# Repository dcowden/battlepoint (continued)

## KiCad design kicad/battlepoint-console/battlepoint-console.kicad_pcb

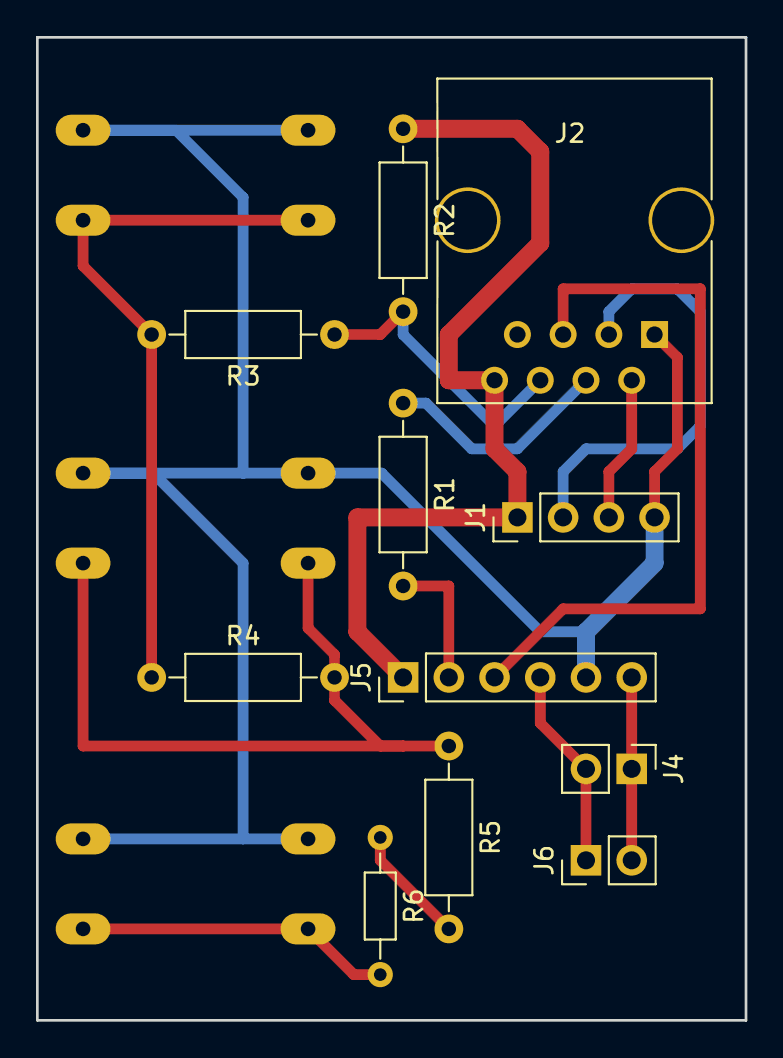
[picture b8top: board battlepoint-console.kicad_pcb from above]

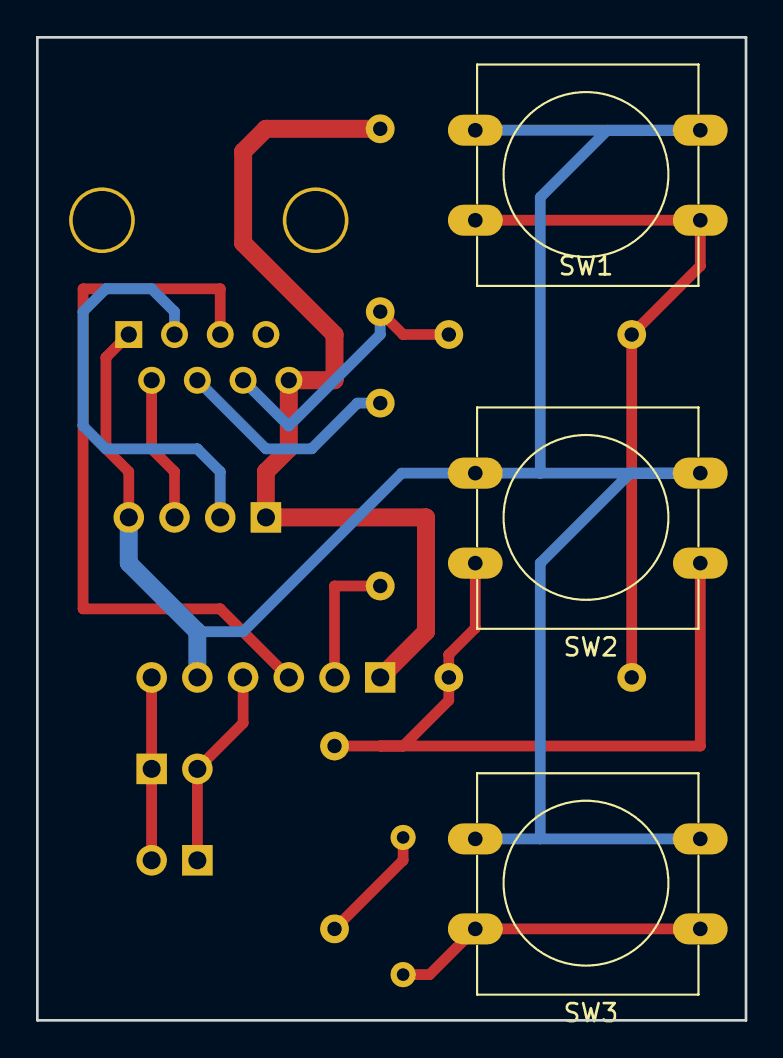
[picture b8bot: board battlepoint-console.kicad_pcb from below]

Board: 2 copper layers, 39.4 x 54.6 mm, 14 parts (3 on the bottom side), 14 nets.

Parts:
J1: OLED; Pin_Header_Straight_1x04_Pitch2.54mm
J2: TOMAIN; RJ45_8
J4: SPK; Pin_Header_Straight_1x02_Pitch2.54mm
J5: DFP; Pin_Header_Straight_1x06_Pitch2.54mm
J6: EXT_AUD; Pin_Header_Straight_1x02_Pitch2.54mm
R1, R5: 1K; R_Axial_DIN0207_L6.3mm_D2.5mm_P10.16mm_Horizontal
R2: 2K; R_Axial_DIN0207_L6.3mm_D2.5mm_P10.16mm_Horizontal
R3: 330; R_Axial_DIN0207_L6.3mm_D2.5mm_P10.16mm_Horizontal
R4: 620; R_Axial_DIN0207_L6.3mm_D2.5mm_P10.16mm_Horizontal
R6: 3.3K; R_Axial_DIN0204_L3.6mm_D1.6mm_P7.62mm_Horizontal
SW1: SW_UP; SW_PUSH-12mm
SW2: SW_DOWN; SW_PUSH-12mm
SW3: SW_SELECT; SW_PUSH-12mm

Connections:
+5V: J1.1, J2.8, J5.1, R2.1
A0: J2.6, R2.2, R3.1
GND: J1.4, J2.1, J5.5, SW1.2, SW2.2, SW3.2
unnamed: J1.2, J2.3
unnamed: J1.3, J2.2
unnamed: J2.4, R1.1
unnamed: J2.5, J5.3
unnamed: J5.2, R1.2
unnamed: R3.2, R4.1, SW1.1
unnamed: R4.2, R5.1, SW2.1
unnamed: R5.2, R6.1
unnamed: R6.2, SW3.1
SPK+: J4.2, J5.4, J6.1
SPK-: J4.1, J5.6, J6.2

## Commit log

2017-11-23 initial version
2017-11-23 vscode
2017-11-23 removed duplicate
2017-11-23 test commit
2017-11-23 another test commit
2017-11-23 removed duplciate
2017-12-03 trying to get nodemcu to work
2017-12-06 added kicad stuff
2017-12-07 working mostly
2017-12-07 progress
2017-12-07 about to start routing
2017-12-08 finished for now i think
2017-12-09 used rj45s for connections
2017-12-09 moved stuff
2017-12-09 more compact layout
2017-12-09 made button board fit
2017-12-10 got button board working
2017-12-15 base version without regulator
2017-12-15 add regulator circuit
2017-12-15 made the pads bigger
2017-12-17 version 1.0
2017-12-17 reversed the top layer
2017-12-17 fix missing traces on front
2017-12-23 version 1.2 finally ready!
2017-12-23 added todo
2017-12-23 more todo
2017-12-23 starting to clean up the code
2017-12-23 new boards
2017-12-23 suggestions for next version
2017-12-23 new script
2017-12-23 small mods to sound script
2017-12-30 changed to usb connectors
2017-12-31 routed
2018-01-01 finished routing
2018-06-03 added ledmeter
2018-06-03 mostly compiles now
2018-06-18 working on unit testing
2018-06-18 tests pass now
2018-06-18 tests working, nicer now
2018-06-18 added test for initial state
2018-06-20 working on refactoring
2018-06-21 a bit more progress
2018-06-22 more progress
2018-06-23 most control point tests working now
2018-06-23 timer and game audio passing tests now
2018-06-24 started on game
2018-06-24 most of the game stuff refactored
2018-06-24 mostly there
2018-06-25 tests passing again
2018-06-25 add classes to make testing easier
2018-06-25 control point easier to test. added test event manager
2018-06-26 got game init to work
2018-07-03 added more game tests
2018-07-03 new tests passing now
2018-07-04 added a clock
2018-07-04 add game clock
2018-07-04 added fake clock. passing.
2018-07-05 passing tests
2018-07-07 tests for games now passing
2018-07-07 add rotary library and menu library
2018-07-15 game display
2021-06-26 refactor. include all the old things
2021-06-26 used payload nerfcon3 version
2021-06-27 LedMeter Tests Working
2021-06-28 integrated hit tester
2021-06-28 integrated fft
2021-06-30 fft based detection
2021-07-02 target code working
2021-07-02 Added button
2021-07-02 tests passing for target, button, meter, clock
2021-07-04 working towards first game
2021-07-05 Last Version before collapsing
2021-07-05 moved to simpler strategy for data and game
2021-07-05 tests passing
2021-07-08 basic loop working state machien sucks though
2021-07-08 added display update
2021-07-08 fixed led display
2021-07-22 added other menu entries
2021-07-22 added flash settings to meter
2021-07-22 refactored
2021-07-22 fix tests
2021-07-22 added settings. removed appmode.
2021-07-23 added flasher control for leds
2021-07-23 tests are passing
2021-07-23 added tests for attack/defend, most hits in time, and first to hits games
2021-07-23 changed to hits
2021-07-24 asdf
2021-07-24 added tets for hit decay
2021-07-26 added tests for ownership checking
2021-07-26 ownership mostly working
2021-07-26 some oz tests passing
2021-07-27 all tests passing atm
2021-07-28 added most of meter update code
2021-07-29 before adding a pointer for the led array to ledcontroller
2021-07-29 moved led array pointer into struct
2021-07-29 refactored led update code to make testing easier.
2021-07-29 stupid assertion was wrong!
2021-07-29 fixed bug with left/right switch, and basic meters are working now
2021-07-30 added flashing tests
2021-08-03 fixed flashing test
2021-08-08 moved some stuff out of main
2021-08-08 added target test 'game'
2021-08-08 save settings for target test game too
2021-08-14 added target stuff
2021-08-14 changed target thresholds from double to long
2021-08-14 fixed settings saving. structs are not automatically read by EEPROM.get!
2021-08-15 encoder working finally
2021-08-15 got encoder working
2021-08-15 fixed settings issue. target testing kinda works, but now need to measure for hits in a handler
2021-08-23 got trigger timings right
2021-08-26 fixed some bugs with updating
2021-08-29 leds work now.
2021-09-04 fft working now
2021-09-04 fft working
2021-09-08 added target scanner
2021-09-08 add target scanner
2021-09-09 fixed tests. separated meter code from game logic
2021-09-10 merged controller and ledmeter
2021-09-11 tests passing. using new target scanner
2021-09-12 tests passing and the thing actually works! needs code cleanup
2021-09-13 flashing and decay
2021-09-13 beginning cleanup
2021-09-13 cleanup
2021-09-14 added diagnostics. fixed blinking bug
2021-09-14 remove extra print
2021-09-25 fixed various bugs. set up timing.
2021-09-26 trying out tensorflow
2021-11-21 fixed panic on target serial out
2021-11-26 adding start of clock firmware
2021-11-26 initially compiling version
2021-11-26 added servo update code
2021-11-26 added debug
2021-11-27 compiles and has all the things
2021-11-27 compiles
2021-11-27 fixed logic
2021-11-28 added batt to display
2021-11-28 fixed tests
2021-11-28 saving and not crashing
2021-11-28 fixed color logic. added ascii art digits
2021-11-29 fixed timer for encoder
2021-12-05 added manual digit menu
2021-12-10 servo perf improvements
2021-12-12 adding dial timer
2021-12-13 three games mostly working now
2021-12-13 now the tests pass
2021-12-13 no really it does now
2021-12-13 tests pass
2021-12-13 all game modes work now basically
2021-12-13 fixed serial output to be mainly data
2021-12-17 dial mostly woring .needs refactor!
2021-12-18 results of battle testing
2021-12-18 refresh display after abort
2021-12-18 added sound to clock.
2021-12-18 fix delay on victory
2021-12-18 updated victory pause
2021-12-18 fixed victory message timing and color
2021-12-20 initial sound try
2021-12-20 integrating sound and pregame
2021-12-21 fixed tests. implemented callback handlers
2021-12-22 factored some logic. more tests pass now.
2021-12-22 stupid tests.
2021-12-23 moved from game_init to doing it all within startGame.
2021-12-23 clean up tmp
2021-12-23 ignore pio files
2021-12-23 restsoring old version without the nano
    restsoring old version without the nano
2021-12-24 fixed lots of little annoying bugs. tests pass again.
2023-11-24 start on the respawn device
2023-11-24 most of it is there. just need settings
2023-11-24 add some logging
2023-11-24 this shoudl load settings and save settings
2023-11-24 added the right mario sounds
2023-11-25 added one test
2023-11-25 cleaned up about as much as possible without OO
2023-11-25 this version saves some code using classes
2023-11-25 move mode into ux file
2023-11-25 even shorter code, using vectorized game durations
2023-11-25 clean up old files. hope this works!
2023-11-25 more cleanup
2023-11-25 finally got native tests running. but slow ide
2023-11-26 changes for nano
2023-12-02 This is working satisfactorily
2023-12-02 doulble clicking any buttons counts respawns
2023-12-10 working respawn counter
2023-12-17 commeted it out for all but long respawn
2024-11-24 Working target version!
2024-11-24 remove dead files
2024-11-29 making board
2024-11-30 mostly working
2024-12-17 compiling refactored, but not tested
2024-12-18 more progress but far from working
2024-12-18 this seems to be pretty good!
2024-12-19 added configurable invuln time. fixed meter size bug
2024-12-20 add error checking for card types
2025-10-30 initial control_squares version
2025-11-01 updated code
2025-11-01 arduino files
2025-11-01 missing files
2025-11-02 pio project
2025-11-02 ble control square working!
2025-11-03 tests pass. koth mostly debugged
2025-11-03 cleaning up
2025-11-07 progress but annoying
2025-11-08 getting ready to start more app changes
2025-11-08 mostly working, even overtime for KOTH
2025-11-08 ui optimized for HD
2025-11-09 added capture multiplier
2025-11-09 tested x2 capture. commented out debug
2025-11-09 added mobile view
2025-11-09 added mobile view. added shoe clip and press switch
2025-11-10 broadcast music working now. the user gesture thing is odd
2025-11-10 fixed duplicate dismiss bug. sound chip working.
2025-11-12 designed board
2025-11-12 added another pin to trigger
2025-11-13 added voltage regulator
2025-11-13 touch up pads
2025-11-14 fixed mirroring
2025-11-14 this seems to work for both switches and qmc now
2025-11-14 fixed issues with board
2025-11-14 add setup script for remote
2025-11-14 added setup file
2025-11-15 faster scans
2025-11-15 updates to scanner
2025-11-15 revive the payload. fiddling with mag sensors again
2025-11-16 firmware give up on red and blue via magnet
2025-11-16 filter based on name prefix
2025-11-17 kinda a starting point!
2025-11-20 fix bug with mixed callbacks
2025-11-20 finally happy with CS board
2025-11-20 programmed the tiles!
2025-11-21 clock game mode added
2025-11-21 mostly working 3cp game
2025-11-21 autodetection
2025-11-21 i think the box is good. blescanner fixed to auto-detect port
2025-11-22 cs_improve
2025-11-22 added browser sound
2025-11-22 switched to browser sound system
2025-11-23 added ad game mode
2025-11-23 make initial layout fit on HD screen. fix toggle button bug
2025-11-23 fixed sound on landing page
2025-11-25 moved pages out to separate modules
2025-11-25 add git ignore
2025-11-25 ignore more files
2025-11-25 try again to fix sound in browser
2025-11-25 sorted music stuffs
2025-11-25 ah! supress nicegui running default browser
2025-11-25 bind to all host addresses
2025-11-25 great starting point for mobile
2025-11-25 goo start on mobile version
2025-11-25 add end of game timer for competitive runs
2025-11-25 fixed bug
2025-11-25 saving key config files
2025-11-26 fix koth display capture meter. fix logic bug in 3cp.
2025-11-26 changed urls to be relative so we can change port and host easily in util
2025-11-27 fix a couple of bugs. make nicer displays
2025-11-27 adding some cad files
2025-11-27 fix presence/capture bug
2025-11-27 add a few missing sounds
2025-11-27 messages for future games-- control point cant own messages any more
2025-11-28 re-fixed weird isssue with koth 2x capture
2025-11-29 added missing stuff
2025-11-29 add qr codes page
2025-11-29 add qrs to landing page
2025-11-29 assume well use bluedirt mobile'
2025-11-29 cache the qrs
